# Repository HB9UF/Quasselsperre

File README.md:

# Introduction

Quasselsperre is an AVR ATtiny-based timeout-timer watchdog, i.e. hardware
circuitry to clear PTT in case it is asserted for an extended amount of time.
This is useful e.g. in a repeater controller, or in an EchoLink interface
controlled by a Raspberry Pi. In case the Raspberry Pi locks up and asserts PTT
indefinitely In case the Raspberry Pi locks up and asserts PTT indefinitely,
this circuit kicks in and disables the transmitter until PTT is cleared.

One may argue that is is better to implement this in hardware instead of
firmware, e.g. with a binary counter such as the CD4060. We chose to do this
in a dedicated microcontroller.

# Pinout

The project is based on an [AVR ATtiny 10](https://www.microchip.com/wwwproducts/en/ATtiny10)
microcontroller with the following pinout:

| Pin number | Pin name | Function                                                                                                |
|----------- | -------- | ------------------------------------------------------------------------------------------------------- |
|          1 | PB0      | Status LED. Connect to LED cathode(!)                                                                   |
|          2 | GND      | Connect to ground                                                                                       |
|          3 | PB1      | PTT output, active high. Connect to base of BJT or gate of FET for open-collector/open-base operation   |
|          4 | PB2      | PTT input, active high. Expects a control voltage ≤ VCC from repeater controller or raspberry pi        |
|          5 | VCC      | Supply voltage, 1.8 V to 5.5 V                                                                          |
|          6 | PB3      | ADC input, see text. Do not leave floating                                                              |

The two input pins must not be left floating.  Add a pull-down if there is any
chance for the PTT input driver to become Hi-Z. On startup, the voltage on the
ADC input is sensed and the timeout delay (i.e. the time after which the watchdog
kicks in) is set according to the following rule: The voltage range between GND
is divided into 8 sub-ranges. If the voltage falls within the lowest range, the
timer is set to 15 minutes. The next range allows for a transmit duration of
30 minutes; each subsequent range add another 15 minutes, yielding a maximal
transmit duration of 2 hours. The pin can be tied low or high with a single
resistor for 15 minutes or 2 hours, respectively, or a resistive divider /
potentiometer can be used to set intermediate values. On startup, the LED
flashes once for each 15 minutes. The pin is only read on startup.

Beware that the LED output pin will sink current: It is Hi-Z when the LED is off
and grounded when the LED is on. In consequence, the LED cathode must connect
to this pin and the LED anode must connect to VCC, of course in series with the
usual current limiting resistor. The PTT output pin is connected to a transistor
as indicated in the table above.

# Compiling and programming

Run the `make` command to compile the firmware. This requires `avr-gcc` along
with the corresponding AVR standard libraries. Alternatively, a pre-compiled
firmware binary is available in the Release-section of the github project page.

Use your programmer and programming software of choice to load the firmware
into the chip. E.g. with `avrdude` and an AVR ISP 2, the following command
can be used:

```
avrdude -c avrisp2 -P usb -p t10 -U flash:w:quasselsperre.hex:i
```

For the ADC functionality to work as indicated above, the `RSTDISBL` fuse must
be used since the ADC pin is also the reset pin:

```
avrdude -c avrisp2 -P usb -p t10 -U fuse:w:0xfe:m
```

Note that after this, you will not be able to reprogram the microcontroller
unless you use the 12 V high-voltage programming option. Since Quasselsperre
has a single, simple task, we believe this to be an acceptable compromise –
the microcontroller probably needs to be programmed a single time or could
even be ordered pre-programmed. For programming, we provide a small jig in the
`programming_jig` subdirectory: The chip can be momentarily pressed onto the
pads of a SOT-23-6 footprint on the jig while the programming takes place.

# License

The Quasselperre code is licensed under the terms of the GPLv2 license. The
artwork for the programming jig is released under the terms of the CC-BY-SA
license. © 2020.

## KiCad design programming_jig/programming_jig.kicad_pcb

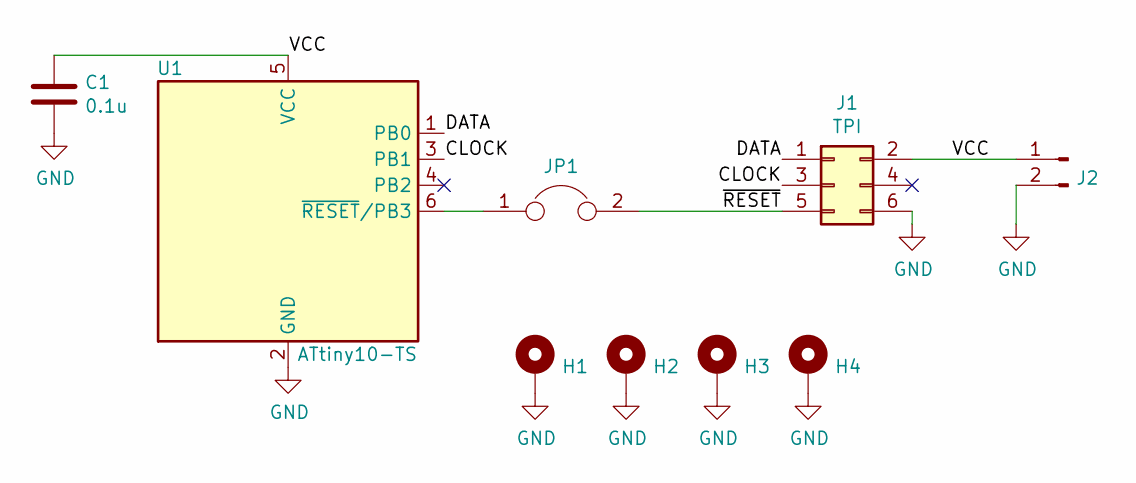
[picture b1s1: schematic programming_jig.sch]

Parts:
C1: 0.1u; C_0603_1608Metric_Pad1.05x0.95mm_HandSolder
H1, H2, H3, H4: MountingHole_Pad; MountingHole_2.5mm_Pad_Via
J1: TPI; IDC-Header_2x03_P2.54mm_Vertical
J2: Conn_01x02_Male; PinHeader_1x02_P2.54mm_Vertical
JP1: Jumper; PinHeader_1x02_P2.54mm_Vertical
U1: ATtiny10-TS; SOT-23-6_Handsoldering

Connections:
/CLOCK: J1.3, U1.3 (PB1)
/DATA: J1.1, U1.1 (PB0)
/VCC: C1.1, J1.2, J2.1, U1.5 (VCC)
/~RESET: J1.5, JP1.2
GND: C1.2, H1.1, H2.1, H3.1, H4.1, J1.6, J2.2, U1.2 (GND)
unnamed: JP1.1, U1.6 (~RESET~/PB3)

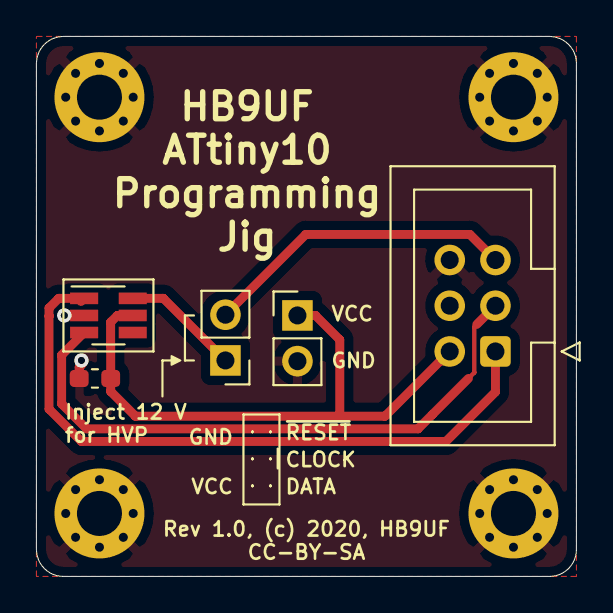
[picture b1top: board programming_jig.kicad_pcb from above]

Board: 2 copper layers, 30.0 x 30.0 mm, 10 parts (1 on the bottom side), 6 nets.

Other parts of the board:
CC-BY-SA-LOGO: Logo_silk_CC-BY-SA_10x4.5mm

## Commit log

2025-01-04 Bugfix: Use correct expression to disable timer
    Due to a wrongly crafted bitmasking expression, timer function
    timer_stop_and_reset() did reset the timer without stopping it. This led
    to intermittent erratic PTT control that was very challenging to track
    down. Pascal HB9HCG was dedicated enough for us to finally track it
    down and fix it.
    The failure mode was as follows: After clearing of PTT, the timeout

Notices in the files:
programming_jig/programming_jig.kicad_pcb:
Rev 1.0, (c) 2020, HB9UF
CC-BY-SA
